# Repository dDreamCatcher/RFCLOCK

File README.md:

### OVERVIEW

RFClock is highly accurate time, phase and frequency synchronization platform as a stand-alone hardware solution that can be interfaced with distributed COTS SDRs.

### HARDWARE
RFClock schematic is in [Hardware](Hardware/schematic-1.png)

### Implementation
RFClock Implementation detail is in [Implementation](Implementation/RFClock_implementation.txt)

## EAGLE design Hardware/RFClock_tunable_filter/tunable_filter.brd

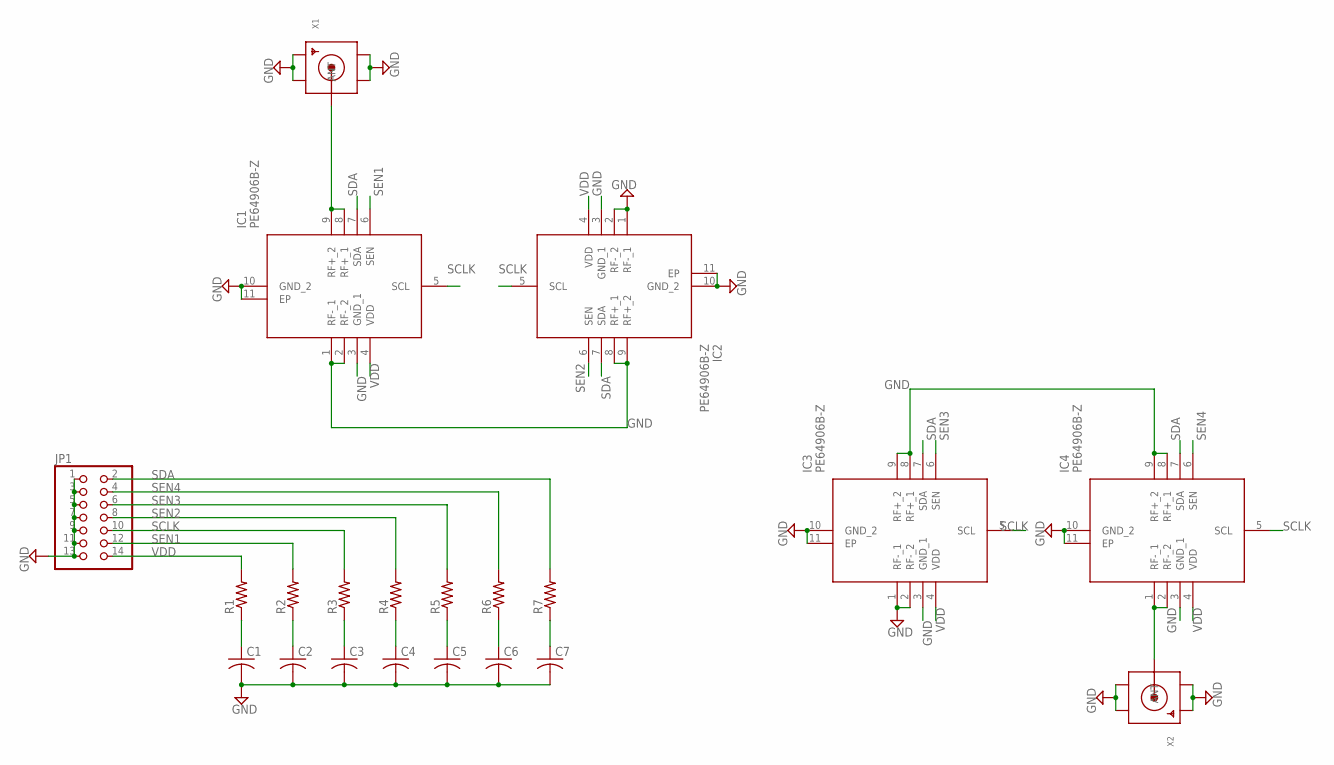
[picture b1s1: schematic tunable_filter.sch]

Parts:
C1, C2, C3, C4, C5, C6, C7: C-USC0402K; C0402K
IC1, IC2, IC3, IC4: PE64906B-Z; QFN50P200X200X60-11N
JP1: PINHD-2X7; 2X07
R1, R2, R3, R4, R5, R6, R7: R-US_R0402; R0402
X1, X2: SMACONNECTOR_EDGE; SMA_EDGELAUNCH

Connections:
GND: C1.2, C2.2, C3.2, C4.2, C5.2, C6.2, C7.2, IC1.1 (RF-_1), IC1.2 (RF-_2), IC1.3 (GND_1), IC1.10 (GND_2), IC1.11 (EP), IC2.1 (RF-_1), IC2.2 (RF-_2), IC2.3 (GND_1), IC2.8 (RF+_1), IC2.9 (RF+_2), IC2.10 (GND_2), IC2.11 (EP), IC3.1 (RF-_1), IC3.2 (RF-_2), IC3.3 (GND_1), IC3.8 (RF+_1), IC3.9 (RF+_2), IC3.10 (GND_2), IC3.11 (EP), IC4.3 (GND_1), IC4.8 (RF+_1), IC4.9 (RF+_2), IC4.10 (GND_2), IC4.11 (EP), JP1.1, JP1.3, JP1.5, JP1.7, JP1.9, JP1.11, JP1.13, X1.GND@1 (GND4), X1.GND@2 (GND3), X1.GND@3 (GND2), X1.GND@4 (GND1), X2.GND@1 (GND4), X2.GND@2 (GND3), X2.GND@3 (GND2), X2.GND@4 (GND1)
unnamed: IC1.8 (RF+_1), IC1.9 (RF+_2), X1.P (ANT)
unnamed: C1.1, R1.1
unnamed: C2.1, R2.1
unnamed: C3.1, R3.1
unnamed: IC4.1 (RF-_1), IC4.2 (RF-_2), X2.P (ANT)
unnamed: C4.1, R4.1
unnamed: C5.1, R5.1
unnamed: C6.1, R6.1
unnamed: C7.1, R7.1
SCLK: IC1.5 (SCL), IC2.5 (SCL), IC3.5 (SCL), IC4.5 (SCL), JP1.10, R3.2
SDA: IC1.7 (SDA), IC2.7 (SDA), IC3.7 (SDA), IC4.7 (SDA), JP1.2, R7.2
SEN1: IC1.6 (SEN), JP1.12, R2.2
SEN2: IC2.6 (SEN), JP1.8, R4.2
SEN3: IC3.6 (SEN), JP1.6, R5.2
SEN4: IC4.6 (SEN), JP1.4, R6.2
VDD: IC1.4 (VDD), IC2.4 (VDD), IC3.4 (VDD), IC4.4 (VDD), JP1.14, R1.2

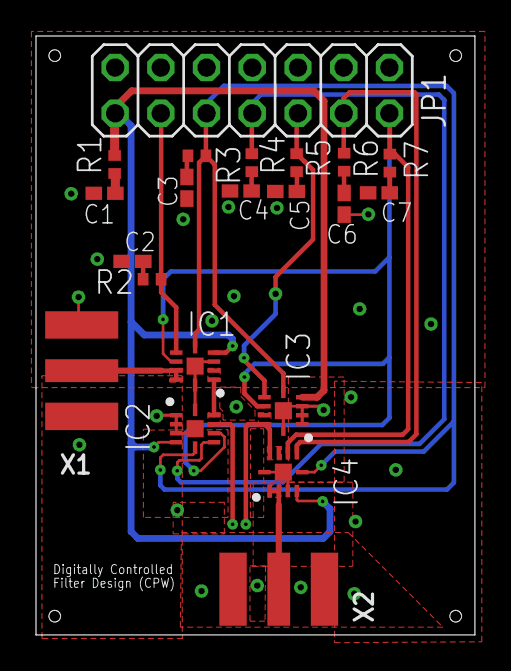
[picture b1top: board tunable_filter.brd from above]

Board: 4 copper layers, 24.4 x 33.3 mm, 21 parts (0 on the bottom side), 17 nets.

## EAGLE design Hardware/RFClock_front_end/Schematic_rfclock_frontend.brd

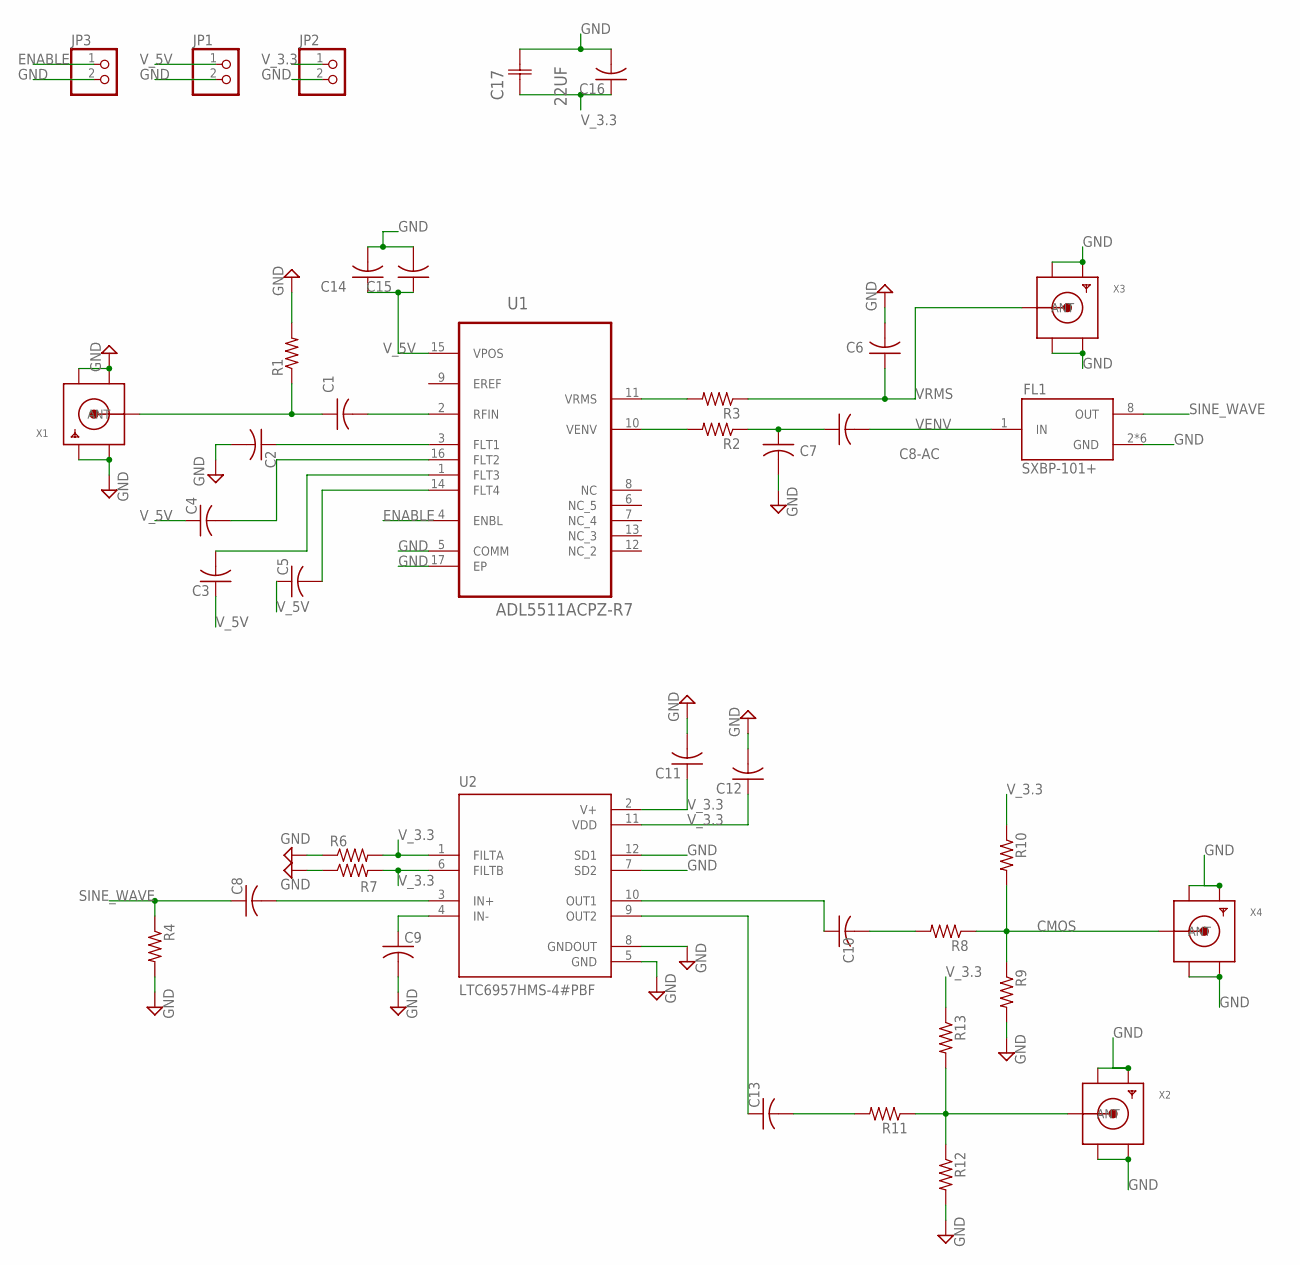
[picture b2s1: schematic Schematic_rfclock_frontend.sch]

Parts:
C1, C2, C8-AC: C-USC0402K; C0402K
C3, C4, C5, C6, C7, C14, C15: C-USC0402; C0402
C8, C9, C16: C-USC0603; C0603
C10, C11, C12, C13: C-USC0603K; C0603K
C17: 22UF; CAPCP3528X210N
FL1: SXBP-101+; FIL_SXBP-101+
JP1, JP2, JP3: PINHD-1X2; 1X02
R1, R2, R3: R-US_R0402; R0402
R4, R6, R7, R8, R9, R10, R11, R12, R13: R-US_R0603; R0603
U1: ADL5511ACPZ-R7; QFN50P300X300X80-17N
U2: LTC6957HMS-4#PBF; SOP65P490X110-12N
X1, X2, X3, X4: SMACONNECTOR_EDGE; SMA_EDGELAUNCH

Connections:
CMOS: R8.1, R9.1, R10.2, X4.P (ANT)
ENABLE: JP3.1, U1.4 (ENBL)
GND: C2.2, C6.2, C7.2, C9.2, C11.2, C12.2, C14.2, C15.2, C16.2, C17.2 (C2), FL1.2 (GND), FL1.3 (GND), FL1.4 (GND), FL1.5 (GND), FL1.6 (GND), FL1.7 (GND), JP1.2, JP2.2, JP3.2, R1.2, R4.2, R6.1, R7.1, R9.2, R12.2, U1.5 (COMM), U1.17 (EP), U2.5 (GND), U2.7 (SD2), U2.8 (GNDOUT), U2.12 (SD1), X1.GND@1 (GND4), X1.GND@2 (GND3), X1.GND@3 (GND2), X1.GND@4 (GND1), X2.GND@1 (GND4), X2.GND@2 (GND3), X2.GND@3 (GND2), X2.GND@4 (GND1), X3.GND@1 (GND4), X3.GND@2 (GND3), X3.GND@3 (GND2), X3.GND@4 (GND1), X4.GND@1 (GND4), X4.GND@2 (GND3), X4.GND@3 (GND2), X4.GND@4 (GND1)
unnamed: C1.2, U1.2 (RFIN)
unnamed: C2.1, U1.3 (FLT1)
unnamed: C1.1, R1.1, X1.P (ANT)
unnamed: C3.2, U1.1 (FLT3)
unnamed: C5.2, U1.14 (FLT4)
unnamed: C4.2, U1.16 (FLT2)
unnamed: R3.2, U1.11 (VRMS)
unnamed: R2.2, U1.10 (VENV)
unnamed: C7.1, C8-AC.1, R2.1
unnamed: C9.1, U2.4 (IN-)
unnamed: C8.2, U2.3 (IN+)
unnamed: C10.1, U2.10 (OUT1)
unnamed: C10.2, R8.2
unnamed: C13.1, U2.9 (OUT2)
unnamed: C13.2, R11.2
unnamed: R11.1, R12.1, R13.2, X2.P (ANT)
SINE_WAVE: C8.1, FL1.8 (OUT), R4.1
VENV: C8-AC.2, FL1.1 (IN)
VRMS: C6.1, R3.1, X3.P (ANT)
V_3.3: C11.1, C12.1, C16.1, C17.1 (C1), JP2.1, R6.2, R7.2, R10.1, R13.1, U2.1 (FILTA), U2.2 (V+), U2.6 (FILTB), U2.11 (VDD)
V_5V: C3.1, C4.1, C5.1, C14.1, C15.1, JP1.1, U1.15 (VPOS)

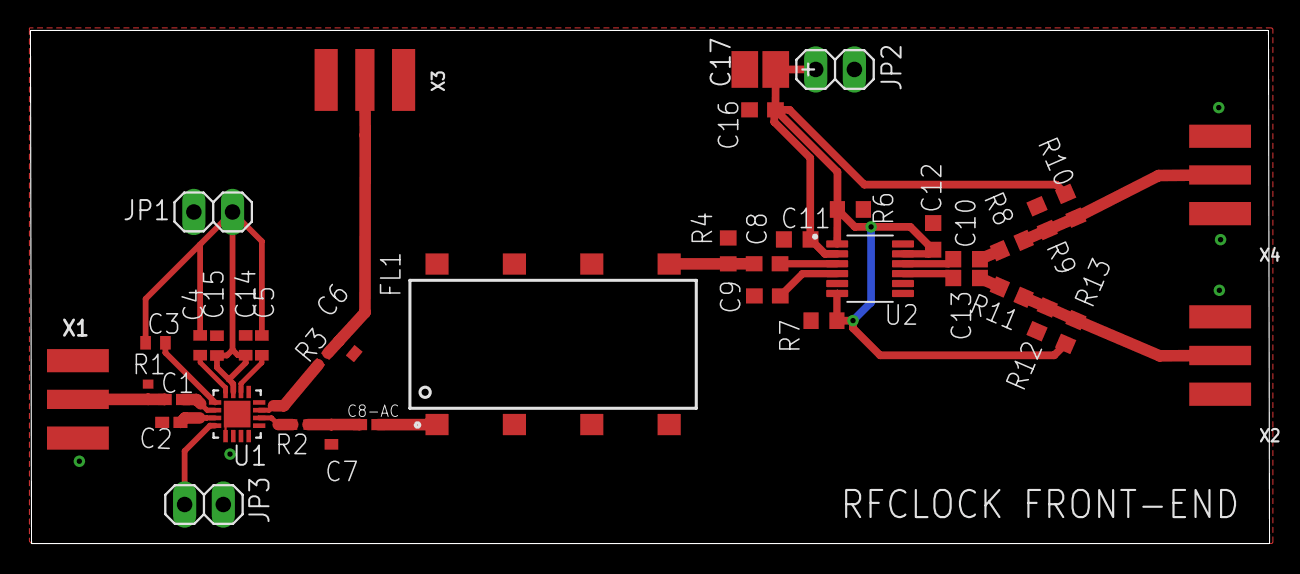
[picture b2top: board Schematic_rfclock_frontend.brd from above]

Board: 2 copper layers, 81.3 x 33.7 mm, 40 parts (0 on the bottom side), 24 nets.

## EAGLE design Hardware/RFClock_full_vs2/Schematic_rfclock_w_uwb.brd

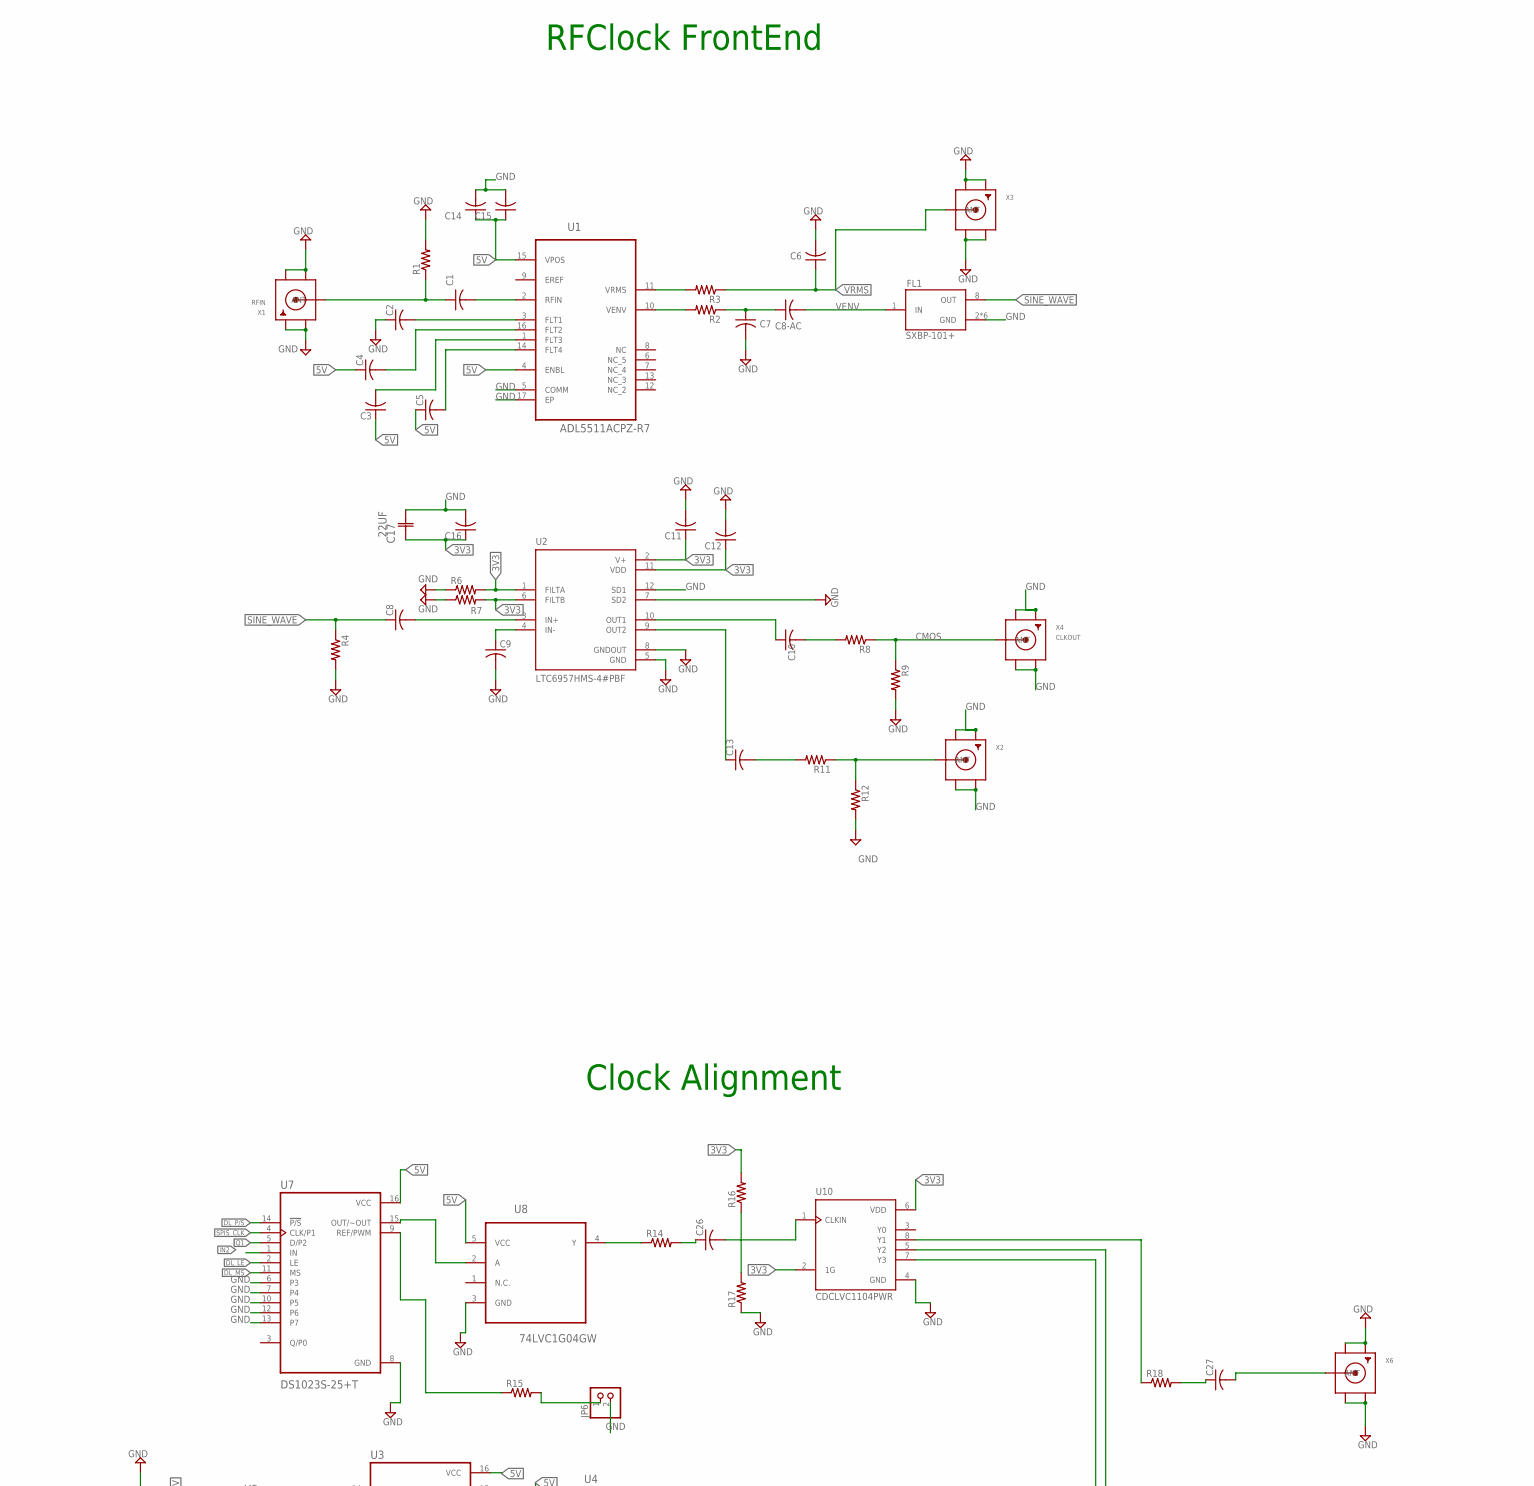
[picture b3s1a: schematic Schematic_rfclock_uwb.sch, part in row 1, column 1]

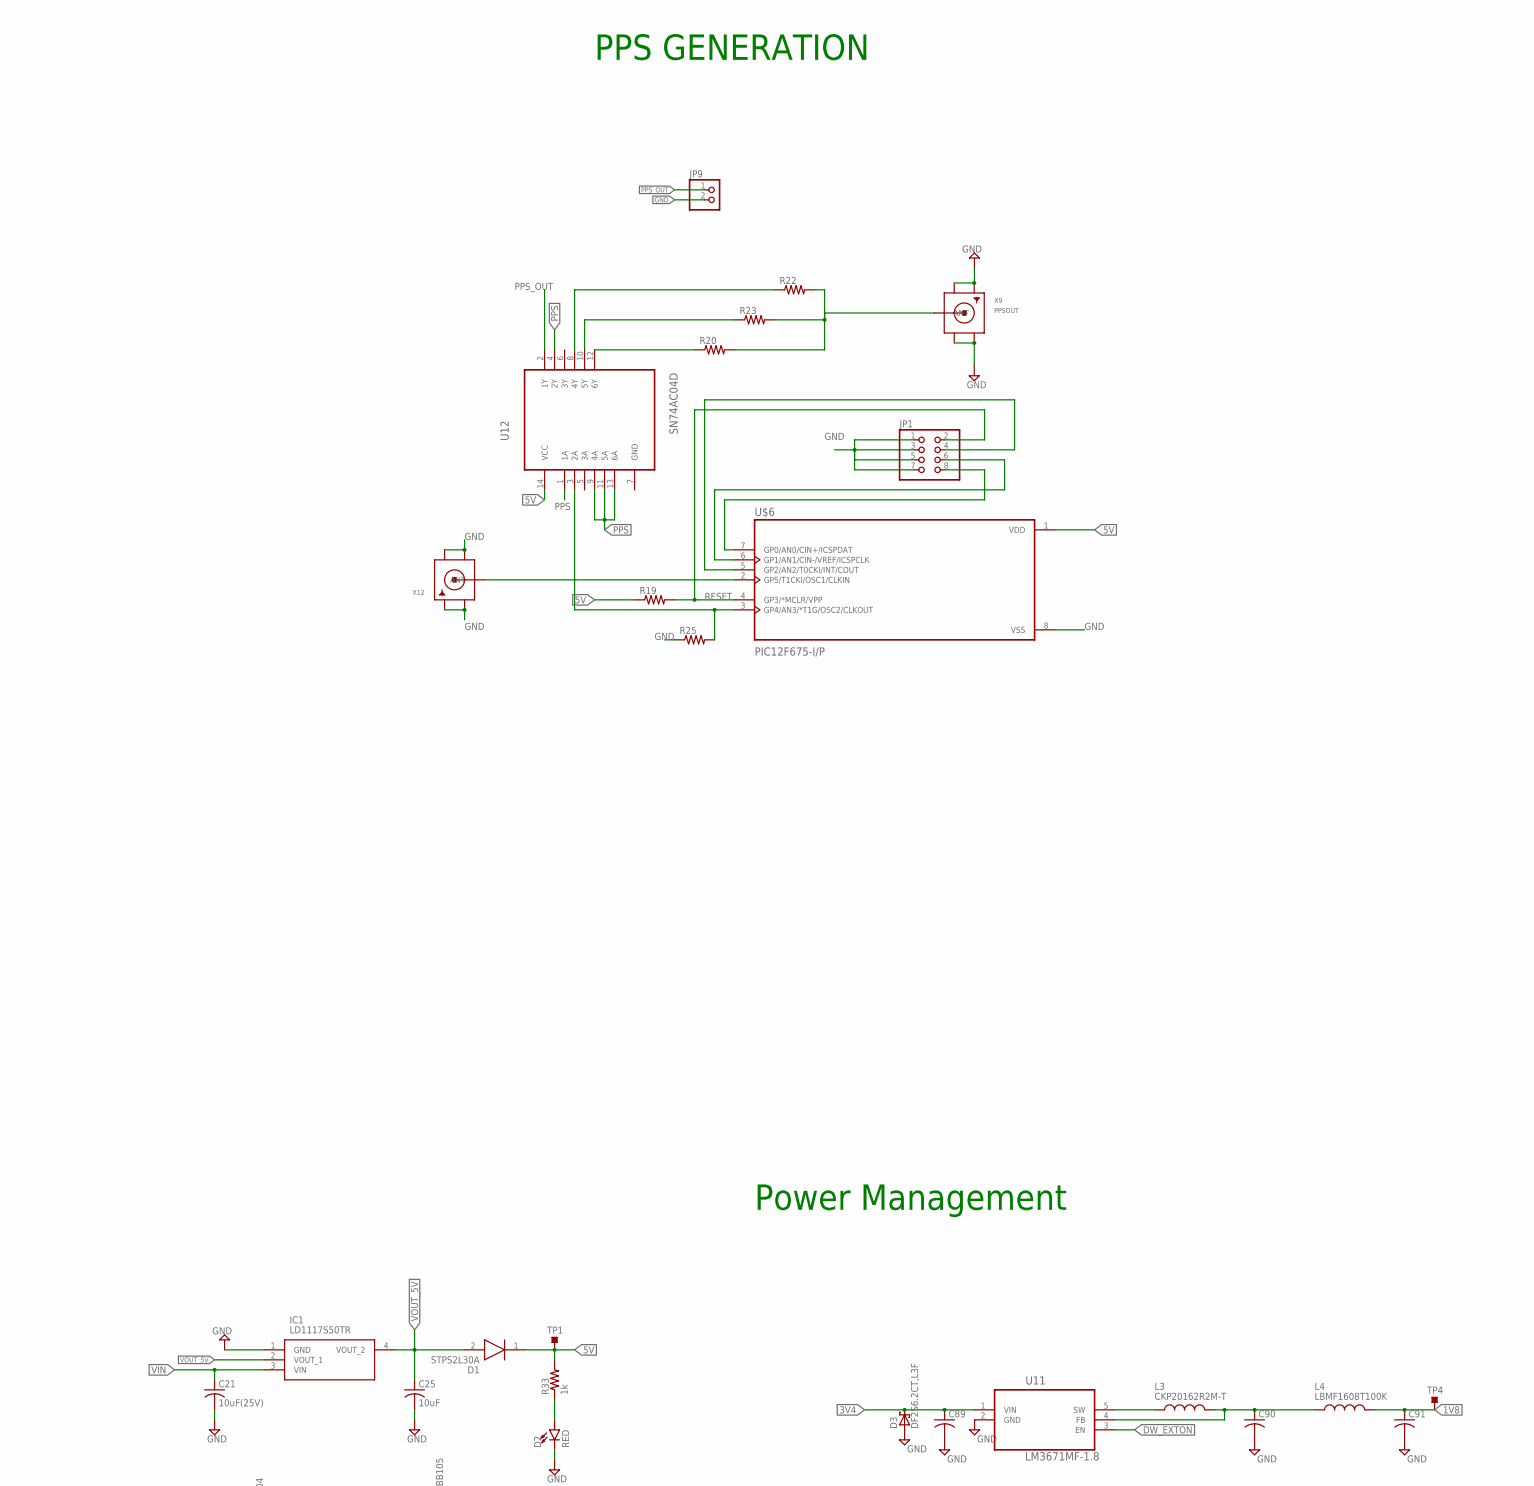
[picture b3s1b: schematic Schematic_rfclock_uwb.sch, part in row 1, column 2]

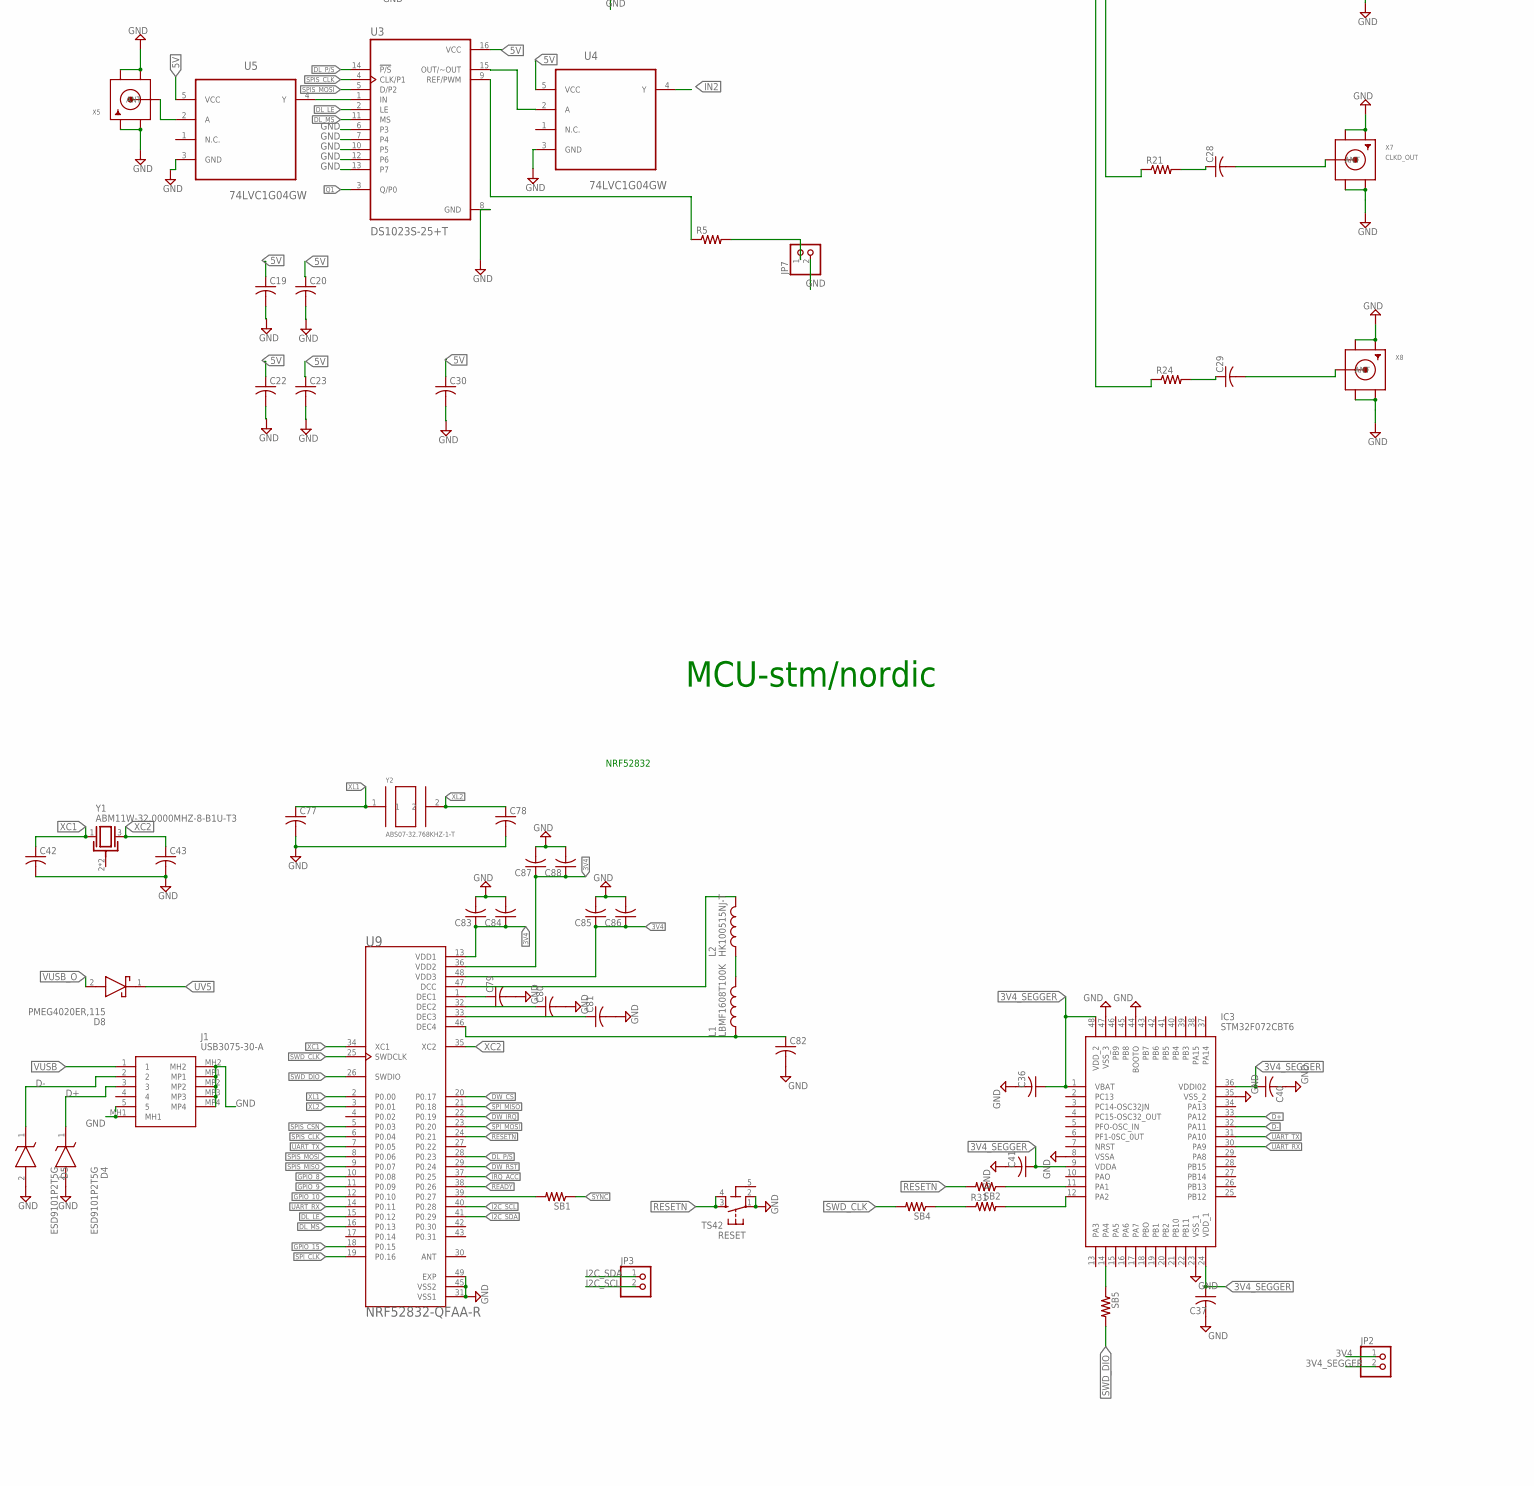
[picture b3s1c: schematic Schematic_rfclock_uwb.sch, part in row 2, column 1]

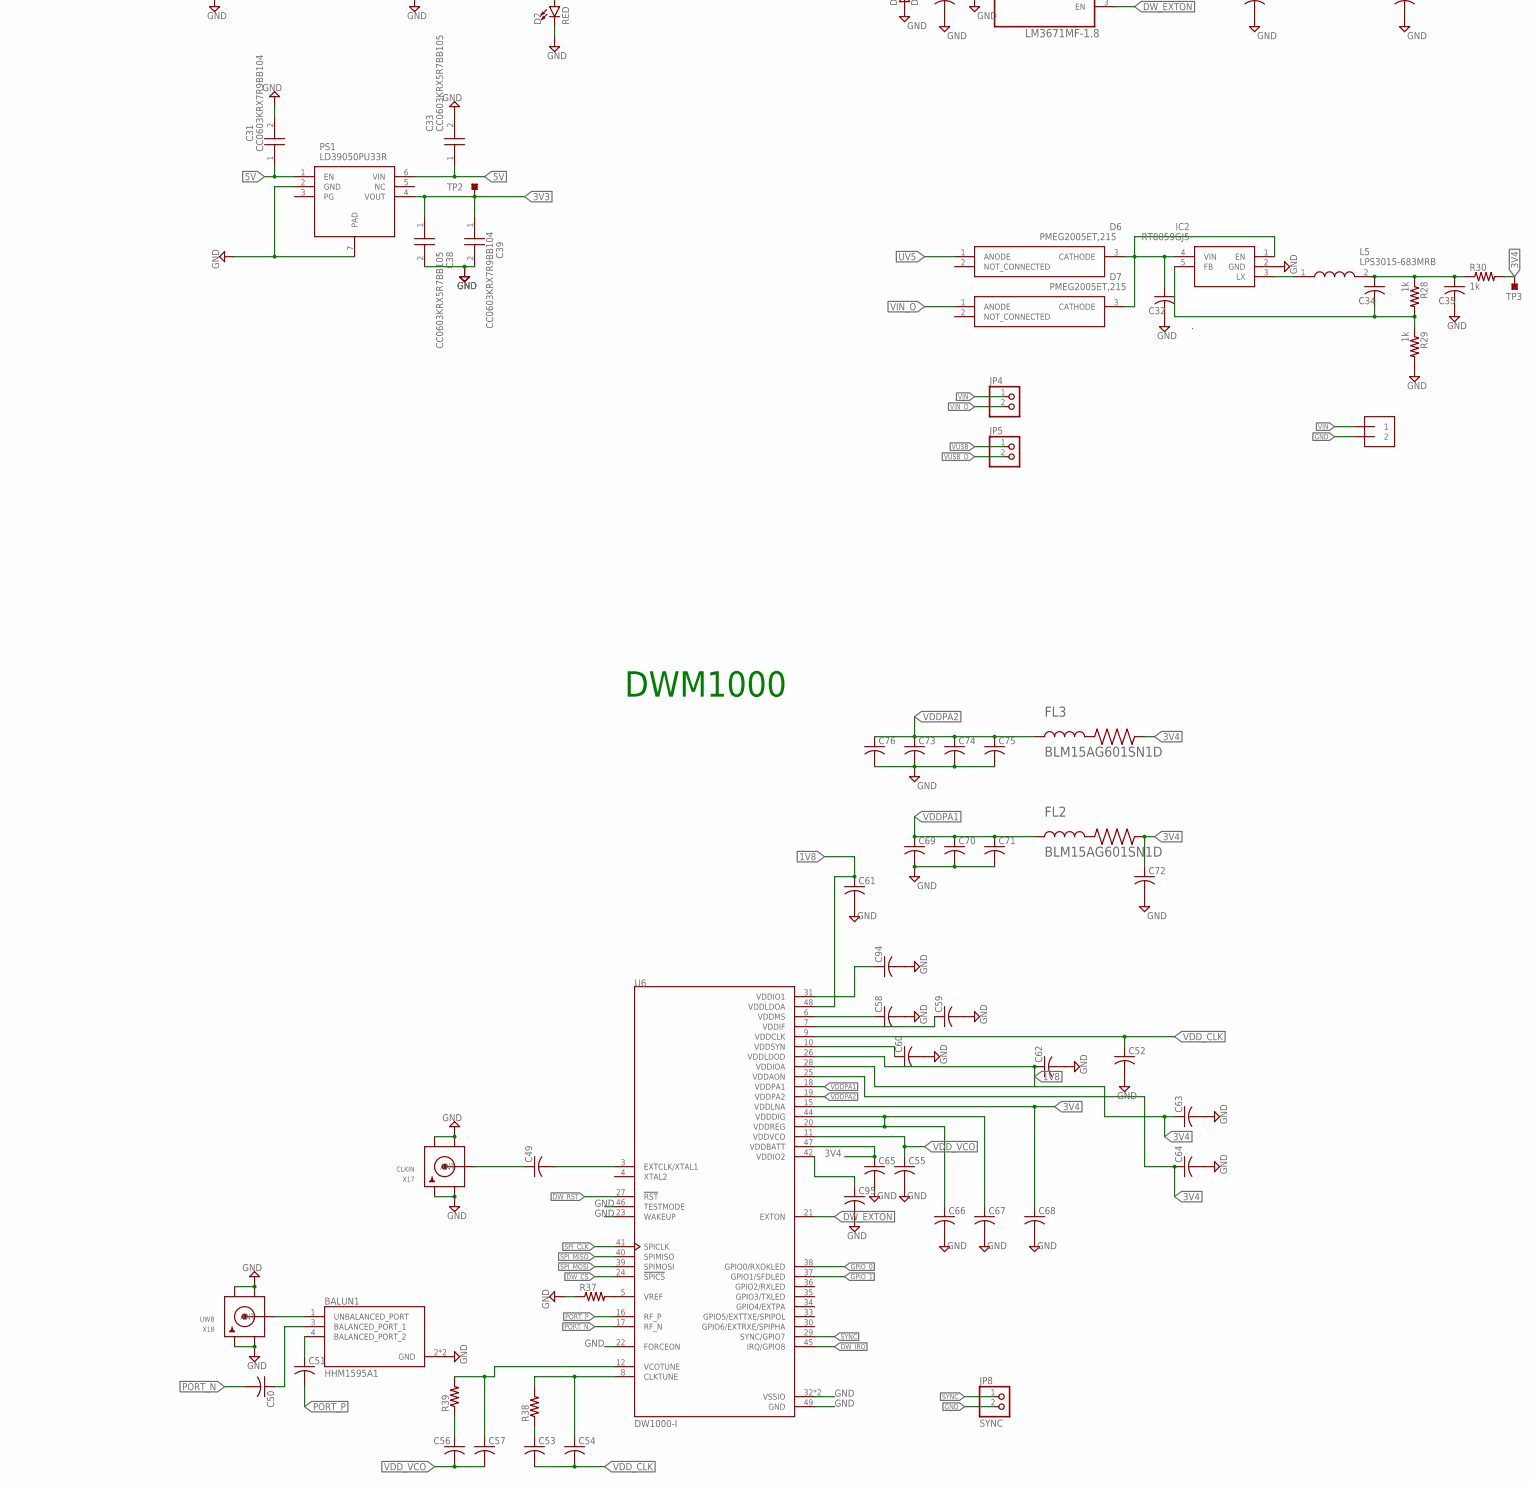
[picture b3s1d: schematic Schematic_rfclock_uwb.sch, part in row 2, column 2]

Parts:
BALUN1: HHM1595A1; BALUN_HHM1595A1
C1, C2, C8-AC, C36, C37, C40, C41, C42, C43, C50, C51, C52, C53, C54, C55, C56, C57, C58, C59, C60, C61, C62, C63, C64, C65, C66, C67, C68, C69, C70, C71, C73, C74, C75, C77, C78, C79, C80, C81, C83, C84, C86, C87, C88, C94, C95: C-USC0402K; C0402K
C3, C4, C5, C6, C7, C14, C15: C-USC0402; C0402
C8, C9, C16, C23: C-USC0603; C0603
C10, C11, C12, C13, C19, C20, C22, C30, C32, C34, C35, C49, C72, C82, C85, C89, C90, C91: C-USC0603K; C0603K
C17: 22UF; CAPCP3528X210N
C21: 10uF(25V); C1210
C25: 10uF; C1206
C26, C27, C28, C29: 1u; C0603
C31, C39: CC0603KRX7R9BB104; CAPC1608X90N
C33, C38: CC0603KRX5R7BB105; CAPC1608X90N
C76: C-USC0805K; C0805K
D1: STPS2L30A; DIOM5126X265N
D2: RED; LED-0603
D3: DF2S6.2CT,L3F
D4, D5: ESD9101P2T5G; SODFL1006X40N
D6, D7: PMEG2005ET,215; SOT95P230X110-3N
D8: PMEG4020ER,115; SODFL3517X110N
FL1: SXBP-101+; FIL_SXBP-101+
FL2, FL3: BLM15AG601SN1D; BEADC1005X55N
IC1: LD1117S50TR; SOT230P700X190-4N
IC2: RT8059GJ5; SOT94P280X100-5N
IC3: STM32F072CBT6; QFP50P900X900X160-48N
J1: USB3075-30-A; USB307530A
J2: 1X2-3.5MM
JP1: PINHD-2X4; 2X04
JP2, JP3, JP4, JP5, JP6, JP7, JP9: PINHD-1X2; 1X02
JP8: SYNC; 1X02
L1, L4: LBMF1608T100K; INDC1608X100N
L2: HK100515NJ-T; INDC1005X55N
L3: CKP20162R2M-T; INDC2016X100N
L5: LPS3015-683MRB; LPS3015683MRB
PS1: LD39050PU33R; SON95P300X300X100-7N
R1, R2, R3, R18, R21, R24, R31, R37, R38, R39: R-US_R0402; R0402
R4, R6, R7, R8, R9, R11, R12, R16, R17, R19, R20, R22, R23, R25: R-US_R0603; R0603
R5, R14, R15: R-US_R0805; R0805
R28, R29, R30, R33: 1k; R0603
RESET: TS42
SB1, SB2, SB4, SB5: R-US_R0402; R0402
TP1, TP2, TP3, TP4: TESTPOINT_TPS-PAD-036; TESTPOINT_PAD-036
U1: ADL5511ACPZ-R7; QFN50P300X300X80-17N
U2: LTC6957HMS-4#PBF; SOP65P490X110-12N
U3, U7: DS1023S-25+T; SOIC127P1032X265-16N
U4, U5, U8: 74LVC1G04GW; SOT65P210X110-5N
U6: DW1000-I; QFN40P600X600X90-49N
U9: NRF52832-QFAA-R; QFN40P600X600X90-49N
U10: CDCLVC1104PWR; SOP65P640X120-8N
U11: LM3671MF-1.8; SOT95P284X122-5N
U12: SN74AC04D; SOIC127P600X175-14N
U$6: PIC12F675-I/P; DIP787W46P254L927H533Q8
X1: RFIN; SMA_EDGELAUNCH
X2: SMACONNECTOR; SMA90_DIP
X3, X5, X6, X8, X12: SMACONNECTOR_EDGE; SMA_EDGELAUNCH
X4: CLKOUT; SMA90_DIP
X7: CLKD_OUT; SMA_EDGELAUNCH
X9: PPSOUT; SMA_EDGELAUNCH
X17: CLKIN; SMA_EDGELAUNCH
X18: UWB; SMA_EDGELAUNCH
Y1: ABM11W-32.0000MHZ-8-B1U-T3; XTAL_ABM11W-32.0000MHZ-8-B1U-T3
Y2: ABS07-32.768KHZ-1-T; XTAL320X150X90

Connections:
1V8: C61.1, C62.1, C91.1, L4.2, TP4.1, U6.26 (VDDLDOD), U6.48 (VDDLDOA)
3V3: C11.1, C12.1, C16.1, C17.1 (C1), C38.1, C39.1, PS1.4 (VOUT), R6.2, R7.2, R16.2, TP2.1, U2.1 (FILTA), U2.2 (V+), U2.6 (FILTB), U2.11 (VDD), U10.2 (1G), U10.6 (VDD)
3V4: C63.1, C64.1, C65.1, C68.1, C72.1, C83.1, C84.1, C85.1, C86.1, C87.1, C88.1, C89.1, D3.2, FL2.2, FL3.2, JP2.1, R30.2, TP3.1, U6.15 (VDDLNA), U6.25 (VDDAON), U6.28 (VDDIOA), U6.47 (VDDBATT), U9.13 (VDD1), U9.36 (VDD2), U9.48 (VDD3), U11.1 (VIN)
3V4_SEGGER: C36.1, C37.1, C40.1, C41.1, IC3.1 (VBAT), IC3.9 (VDDA), IC3.24 (VDD_1), IC3.36 (VDDI02), IC3.48 (VDD_2), JP2.2
5-GND: RESET.5 (5-GND)
5V: C3.1, C4.1, C5.1, C14.1, C15.1, C19.1, C20.1, C22.1, C23.1, C30.1, C31.1, C33.1, D1.1 (K), PS1.1 (EN), PS1.6 (VIN), R19.1, R33.2, TP1.1, U1.4 (ENBL), U1.15 (VPOS), U3.16 (VCC), U4.5 (VCC), U5.5 (VCC), U7.16 (VCC), U8.5 (VCC), U12.14 (VCC), U$6.1 (VDD)
CMOS: R8.1, R9.1, X4.ANTENNA (ANT)
D+: D4.1 (K), IC3.33 (PA12), J1.3
D-: D5.1 (K), IC3.32 (PA11), J1.2
DL_LE: U3.2 (LE), U7.2 (LE), U9.15 (P0.12)
DL_MS: U3.11 (MS), U7.11 (MS), U9.16 (P0.13)
DL_P/S: U3.14 (!P/S), U7.14 (!P/S), U9.28 (P0.23)
DW_CS: U6.24 (!SPICS), U9.20 (P0.17)
DW_EXTON: U6.21 (EXTON), U11.3 (EN)
DW_IRQ: U6.45 (IRQ/GPIO8), U9.22 (P0.19)
DW_RST: U6.27 (!RST), U9.29 (P0.24)
GND: BALUN1.2 (GND), BALUN1.5 (GND), C2.1, C6.2, C7.2, C9.2, C11.2, C12.2, C14.2, C15.2, C16.2, C17.2 (C2), C19.2, C20.2, C21.2, C22.2, C23.2, C25.2, C30.2, C31.2, C32.2, C33.2, C35.2, C36.2, C37.2, C38.2, C39.2, C40.2, C41.2, C42.2, C43.2, C52.2, C55.2, C58.2, C59.2, C60.2, C61.2, C62.2, C63.2, C64.2, C65.2, C66.2, C67.2, C68.2, C69.2, C70.2, C71.2, C72.2, C73.2, C74.2, C75.2, C76.2, C77.2, C78.2, C79.2, C80.2, C81.2, C82.2, C83.2, C84.2, C85.2, C86.2, C87.2, C88.2, C89.2, C90.2, C91.2, C94.2, C95.2, D2.C, D3.1, D4.2 (A), D5.2 (A), FL1.2 (GND), FL1.3 (GND), FL1.4 (GND), FL1.5 (GND), FL1.6 (GND), FL1.7 (GND), IC1.1 (GND), IC2.2 (GND), IC3.8 (VSSA), IC3.23 (VSS_1), IC3.35 (VSS_2), IC3.44 (BOOTO), IC3.47 (VSS_3), J1.MH1, J1.MH2, J1.MP1, J1.MP2, J1.MP3, J1.MP4, J2.2, JP1.1, JP1.3, JP1.5, JP1.7, JP6.2, JP7.2, JP8.2, JP9.2, PS1.2 (GND), PS1.7 (PAD), R1.2, R4.2, R6.1, R7.1, R9.2, R12.2, R17.1, R25.1, R29.2, R37.1, RESET.1, RESET.2, U1.5 (COMM), U1.17 (EP), U2.5 (GND), U2.7 (SD2), U2.8 (GNDOUT), U2.12 (SD1), U3.6 (P3), U3.7 (P4), U3.8 (GND), U3.10 (P5), U3.12 (P6), U3.13 (P7), U4.3 (GND), U5.3 (GND), U6.22 (FORCEON), U6.23 (WAKEUP), U6.32 (VSSIO), U6.43 (VSSIO), U6.46 (TESTMODE), U6.49 (GND), U7.6 (P3), U7.7 (P4), U7.8 (GND), U7.10 (P5), U7.12 (P6), U7.13 (P7), U8.3 (GND), U9.31 (VSS1), U9.45 (VSS2), U9.49 (EXP), U10.4 (GND), U11.2 (GND), U$6.8 (VSS), X1.GND@1 (GND4), X1.GND@2 (GND3), X1.GND@3 (GND2), X1.GND@4 (GND1), X2.GND1, X2.GND2, X2.GND3, X2.GND4, X3.GND@1 (GND4), X3.GND@2 (GND3), X3.GND@3 (GND2), X3.GND@4 (GND1), X4.GND1, X4.GND2, X4.GND3, X4.GND4, X5.GND@1 (GND4), X5.GND@2 (GND3), X5.GND@3 (GND2), X5.GND@4 (GND1), X6.GND@1 (GND4), X6.GND@2 (GND3), X6.GND@3 (GND2), X6.GND@4 (GND1), X7.GND@1 (GND4), X7.GND@2 (GND3), X7.GND@3 (GND2), X7.GND@4 (GND1), X8.GND@1 (GND4), X8.GND@2 (GND3), X8.GND@3 (GND2), X8.GND@4 (GND1), X9.GND@1 (GND4), X9.GND@2 (GND3), X9.GND@3 (GND2), X9.GND@4 (GND1), X12.GND@1 (GND4), X12.GND@2 (GND3), X12.GND@3 (GND2), X12.GND@4 (GND1), X17.GND@1 (GND4), X17.GND@2 (GND3), X17.GND@3 (GND2), X17.GND@4 (GND1), X18.GND@1 (GND4), X18.GND@2 (GND3), X18.GND@3 (GND2), X18.GND@4 (GND1), Y1.2 (GND), Y1.4 (GND)
GPIO_0: U6.38 (GPIO0/RXOKLED)
GPIO_1: U6.37 (GPIO1/SFDLED)
GPIO_8: U9.10 (P0.08)
GPIO_9: U9.11 (P0.09)
GPIO_10: U9.12 (P0.10)
GPIO_15: U9.18 (P0.15)
I2C_SCL: JP3.2, U9.40 (P0.28)
I2C_SDA: JP3.1, U9.41 (P0.29)
IN2: U4.4 (Y), U7.1 (IN)
IRQ_ACC: U9.37 (P0.25)
unnamed: C1.2, U1.2 (RFIN)
unnamed: C2.2, U1.3 (FLT1)
unnamed: C1.1, R1.1, X1.P (ANT)
unnamed: C3.2, U1.1 (FLT3)
unnamed: C5.2, U1.14 (FLT4)
unnamed: C4.2, U1.16 (FLT2)
unnamed: R3.2, U1.11 (VRMS)
unnamed: R2.2, U1.10 (VENV)
unnamed: C7.1, C8-AC.1, R2.1
unnamed: C9.1, U2.4 (IN-)
unnamed: C8.2, U2.3 (IN+)
unnamed: C10.1, U2.10 (OUT1)
unnamed: C10.2, R8.2
unnamed: C13.1, U2.9 (OUT2)
unnamed: C13.2, R11.2
unnamed: R11.1, R12.1, X2.ANTENNA (ANT)
unnamed: U3.15 (OUT/~OUT), U4.2 (A)
unnamed: U3.1 (IN), U5.4 (Y)
unnamed: U5.2 (A), X5.P (ANT)
unnamed: U7.15 (OUT/~OUT), U8.2 (A)
unnamed: R14.1, U8.4 (Y)
unnamed: R15.1, U7.9 (REF/PWM)
unnamed: C32.1, D6.3 (CATHODE), D7.3 (CATHODE), IC2.1 (EN), IC2.4 (VIN)
unnamed: C26.1, R14.2
unnamed: C26.2, R16.1, R17.2, U10.1 (CLKIN)
unnamed: C27.1, R18.2
unnamed: R25.2, U12.3 (2A), U$6.3 (GP4/AN3/*T1G/OSC2/CLKOUT)
unnamed: C28.1, R21.2
unnamed: C28.2, X7.P (ANT)
unnamed: C29.1, R24.2
unnamed: C29.2, X8.P (ANT)
unnamed: R18.1, U10.8 (Y1)
unnamed: R21.1, U10.5 (Y2)
unnamed: R24.1, U10.7 (Y3)
unnamed: JP6.1, R15.2
unnamed: JP7.1, R5.2
unnamed: R5.1, U3.9 (REF/PWM)
unnamed: C27.2, X6.P (ANT)
unnamed: D2.A, R33.1
unnamed: R20.1, U12.12 (6Y)
unnamed: R23.1, U12.10 (5Y)
unnamed: R22.1, U12.8 (4Y)
unnamed: JP1.6, U$6.6 (GP1/AN1/CIN-/VREF/ICSPCLK)
unnamed: R20.2, R22.2, R23.2, X9.P (ANT)
unnamed: JP1.4, U$6.5 (GP2/AN2/T0CKI/INT/COUT)
unnamed: JP1.8, U$6.7 (GP0/AN0/CIN+/ICSPDAT)
unnamed: U$6.2 (GP5/T1CKI/OSC1/CLKIN), X12.P (ANT)
unnamed: C49.1, X17.P (ANT)
unnamed: IC2.3 (LX), L5.1
unnamed: C49.2, U6.3 (EXTCLK/XTAL1)
unnamed: C34.1, C35.1, L5.2, R28.1, R30.1
unnamed: R37.2, U6.5 (VREF)
unnamed: BALUN1.1 (UNBALANCED_PORT), X18.P (ANT)
unnamed: BALUN1.4 (BALANCED_PORT_2), C51.1
unnamed: C53.1, R38.1
unnamed: C57.1, R39.2, U6.12 (VCOTUNE)
unnamed: C56.1, R39.1
unnamed: C94.1, U6.31 (VDDIO1)
unnamed: C58.1, U6.6 (VDDMS)
unnamed: C59.1, U6.7 (VDDIF)
unnamed: C60.1, U6.10 (VDDSYN)
unnamed: C66.1, C67.1, U6.20 (VDDREG), U6.44 (VDDDIG)
unnamed: C79.1, U9.1 (DEC1)
unnamed: C80.1, U9.32 (DEC2)
unnamed: C81.1, U9.33 (DEC3)
unnamed: C82.1, L1.1, U9.46 (DEC4)
unnamed: L1.2, L2.1
unnamed: L2.2, U9.47 (DCC)
unnamed: L3.1, U11.5 (SW)
unnamed: C90.1, L3.2, L4.1, U11.4 (FB)
unnamed: C54.1, R38.2, U6.8 (CLKTUNE)
unnamed: C95.1, U6.42 (VDDIO2)
unnamed: BALUN1.3 (BALANCED_PORT_1), C50.1
unnamed: C34.2, IC2.5 (FB), R28.2, R29.1
unnamed: SB1.2, U9.39 (P0.27)
unnamed: IC3.11 (PA1), SB2.1
unnamed: IC3.12 (PA2), R31.2
unnamed: R31.1, SB4.1
unnamed: IC3.14 (PA4), SB5.1
PORT_N: C50.2, U6.17 (RF_N)
PORT_P: C51.2, U6.16 (RF_P)
PPS: U12.1 (1A), U12.4 (2Y), U12.9 (4A), U12.11 (5A), U12.13 (6A)
PPS_OUT: JP9.1, U12.2 (1Y)
Q1: U3.3 (Q/P0), U7.5 (D/P2)
READY: U9.38 (P0.26)
RESET: JP1.2, R19.2, U$6.4 (GP3/*MCLR/VPP)
RESETN: RESET.3, RESET.4, SB2.2, U9.24 (P0.21)
SINE_WAVE: C8.1, FL1.8 (OUT), R4.1
SPIS_CLK: U3.4 (CLK/P1), U7.4 (CLK/P1), U9.6 (P0.04)
SPIS_CSN: U9.5 (P0.03)
SPIS_MISO: U9.9 (P0.07)
SPIS_MOSI: U3.5 (D/P2), U9.8 (P0.06)
SPI_CLK: U6.41 (SPICLK), U9.19 (P0.16)
SPI_MISO: U6.40 (SPIMISO), U9.21 (P0.18)
SPI_MOSI: U6.39 (SPIMOSI), U9.23 (P0.20)
SWD_CLK: SB4.2, U9.25 (SWDCLK)
SWD_DIO: SB5.2, U9.26 (SWDIO)
SYNC: JP8.1, SB1.1, U6.29 (SYNC/GPIO7)
UART_RX: IC3.30 (PA9), U9.14 (P0.11)
UART_TX: IC3.31 (PA10), U9.7 (P0.05)
UV5: D6.1 (ANODE), D8.1 (K)
VDDPA1: C69.1, C70.1, C71.1, FL2.1, U6.18 (VDDPA1)
VDDPA2: C73.1, C74.1, C75.1, C76.1, FL3.1, U6.19 (VDDPA2)
VDD_CLK: C52.1, C53.2, C54.2, U6.9 (VDDCLK)
VDD_VCO: C55.1, C56.2, C57.2, U6.11 (VDDVCO)
VENV: C8-AC.2, FL1.1 (IN)
VIN: C21.1, IC1.3 (VIN), J2.1, JP4.1
VIN_O: D7.1 (ANODE), JP4.2
VOUT_5V: C25.1, D1.2 (A), IC1.2 (VOUT_1), IC1.4 (VOUT_2)
VRMS: C6.1, R3.1, X3.P (ANT)
VUSB: J1.1, JP5.1
VUSB_O: D8.2 (A), JP5.2
XC1: C42.1, U9.34 (XC1), Y1.1
XC2: C43.1, U9.35 (XC2), Y1.3
XL1: C77.1, U9.2 (P0.00), Y2.1
XL2: C78.1, U9.3 (P0.01), Y2.2

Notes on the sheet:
RFClock FrontEnd
Clock Alignment
PPS GENERATION
MCU-stm/nordic
Power Management
DWM1000
NRF52832

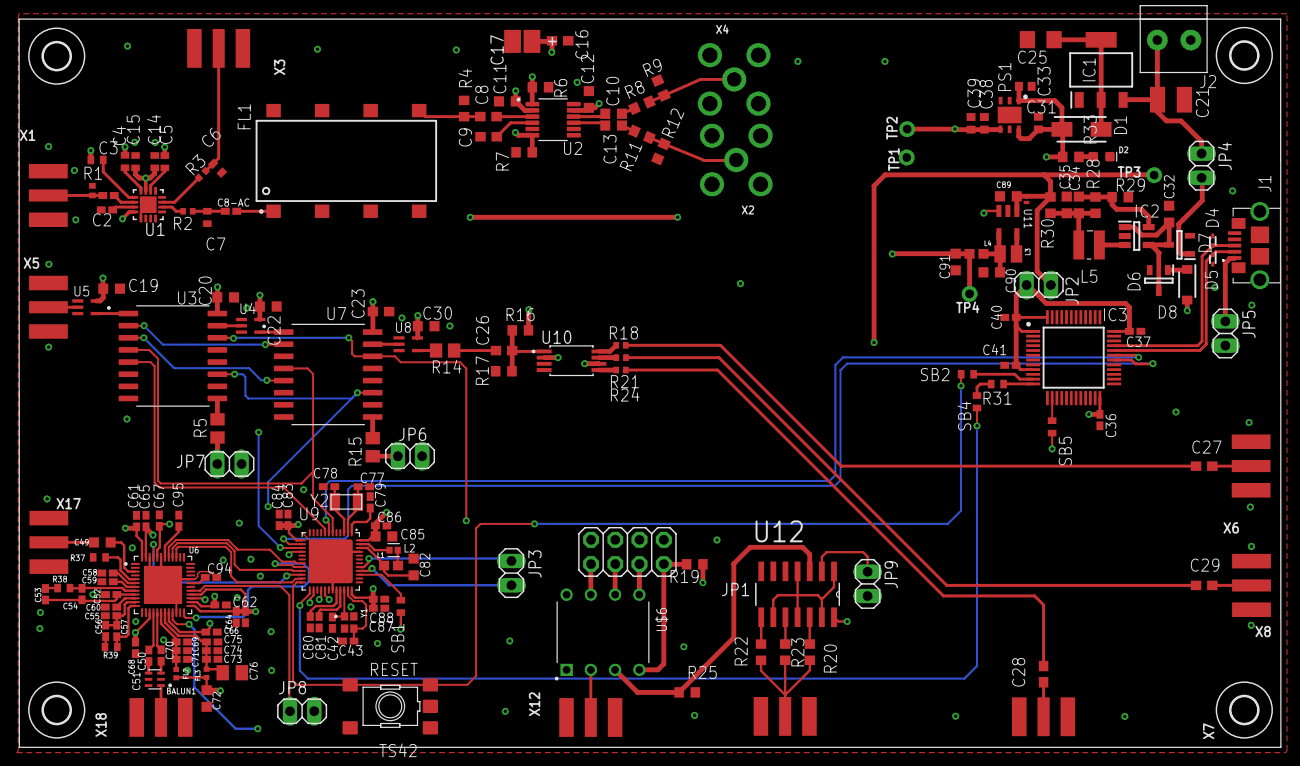
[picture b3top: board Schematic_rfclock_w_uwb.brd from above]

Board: 4 copper layers, 132.1 x 76.2 mm, 190 parts (0 on the bottom side), 132 nets.

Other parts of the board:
U$1, U$2, U$3, U$4: 2,8

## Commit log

2020-08-20 added RFClck files
2020-08-20 image updated
2020-08-20 .html version
2020-08-20 .txt version
2020-08-20 changes in files
2020-08-20 delted files
2020-08-22 added schematics files
2020-08-22 deleted files
2020-08-24 added tof schematic
2020-09-04 updated filter design
2022-01-13 design files updated
2022-01-14 Create LICENSE
2022-01-14 added LICENSE
2022-01-14 Rename LICENSE to LICENSE.md
2024-04-15 some experiment file
2024-08-01 twr message exchange for time sync

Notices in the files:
parts and their libraries:
SparkFun-LED: Licensing: Creative Commons ShareAlike 4.0 International - https://creativecommons.org/licenses/by-sa/4.0
